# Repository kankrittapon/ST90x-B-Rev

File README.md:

# ST909B-4G V1.0 — โน้ตถอดรหัสบอร์ด 4G GPS Tracker (v3)

บอร์ดจริง: **ST909B-4G-V1.0** (silkscreen, วันที่ผลิต 20230816) — แทร็กเกอร์ 4G/GPS ใช้แบตเตอรี่ Li-ion 1 ก้อน
ชิปหลัก: A7670SA (4G LTE Cat-1, SIMCom) + Quectel L76KB-A58 (GNSS) + TP4056 (ชาร์จ) + MCU ตระกูล LQFP-48 (ด้านหลัง, **ถูกถอดออกไปแล้ว**)

เอกสารละเอียดแยกฝั่ง:
- [Front_PCB.md](Front_PCB.md) — ฝั่งหน้า (โมดูล RF, SIM, วงจรชาร์จ, จุดทดสอบ/บริการ)
- [Back_PCB.md](Back_PCB.md) — ฝั่งหลัง (MCU, เสาอากาศ GPS แบบแผ่น, จุดบัดกรีสายเข้าเคส)

เอกสารงาน PCB (ใน `ST909B-4G\`):
- [docs/P3-ROUTING.md](ST909B-4G/docs/P3-ROUTING.md) — เส้นทาง P3 ที่ล็อกแล้ว: ตาราง segment รายชิ้น + กติกา clearance + ข้อพิสูจน์
- [docs/GND-ISLANDS.md](ST909B-4G/docs/GND-ISLANDS.md) — เกาะ GND 4 ชิ้น: โครงสร้าง fill, สาเหตุ, การเย็บ stitching via, วิธี probe
- [docs/P4-SILKSCREEN.md](ST909B-4G/docs/P4-SILKSCREEN.md) — ล้าง silkscreen 42 → 0: กติกากันชน + ตารางย้าย ref/rect ทั้งหมด + sync lib
- [docs/DRC-LOG.md](ST909B-4G/docs/DRC-LOG.md) — วิวัฒนาการ DRC ทุกรอบ + warning ที่ยอมรับ (ตอนนี้เหลือ 2) พร้อมเหตุผล
- `export\` — CSV สถานะล่าสุด (components / nets_pads / routes / drc_violations) + PDF schematic/layers/BOM
- `archive\` — dump ดิบ `.out.txt` (55 ไฟล์) ทุกรอบแก้ + `pads_dump.txt` — ใช้อ้างอิงย้อนหลังเท่านั้น
- `scripts\` — สคริปต์แก้บอร์ด/ตรวจทั้งหมด (หัวไฟล์มีโน้ตการออกแบบ) • รายงาน DRC ปัจจุบันอยู่ที่ `ST909B-4G_drc_violations.json` (รากโปรเจกต์ — อย่าย้าย)

---

## ภาพอ้างอิง (8 ไฟล์)

| ไฟล์ | คำอธิบาย |
|---|---|
| `ภาพทำเองด้านหน้า.jpg` | ภาพวาดฝั่งหน้า + ป้ายกำกับ (แก้ตามรูปจริงแล้ว = v2) |
| `ภาพทำเองด้านหลัง.jpg` | ภาพวาดฝั่งหลัง + ป้ายกำกับ (แก้ตามรูปจริงแล้ว = v2) |
| `ด้านหน้า(บน).jpg` | รูปถ่ายจริงฝั่งหน้าส่วนบน (โมดูล A7670SA, 220µF, +SPK, BOOT) |
| `ด้านหน้า(กลาง).jpg` | รูปถ่ายจริงฝั่งหน้าส่วนกลาง (GPS L76KB, G3V3, SIM slot, LRX/LTX) |
| `ด้านหน้า(ล่าง).jpg` | รูปถ่ายจริงฝั่งหน้าส่วนล่าง (TP4056, M3V3, ขาบริการขอบล่าง) |
| `ด้านหลัง(บน).jpg` | รูปถ่ายจริงฝั่งหลังส่วนบน (ANT-4G, SOS, LED GPS/CHR/4G) |
| `ด้านหลัง(กลาง).jpg` | รูปถ่ายจริงฝั่งหลังส่วนกลาง (แผ่นเสาอากาศ GPS, 0Ω ×2) |
| `ด้านหลัง(ล่าง).jpg` | รูปถ่ายจริงฝั่งหลังส่วนล่าง (MCU footprint, shield fence, MIC) |

---

## สรุปสถานะ (ตรวจครบทุกภาพแล้ว)

### ✅ ยืนยันแล้วจากรูปจริง
- โมดูล **A7670SA** พร้อมข้อมูลฉลากครบ (ดู [Front_PCB.md](Front_PCB.md))
- โมดูล **Quectel L76KB-A58** (ฉลากมาร์ค `L76KB-A58 / 01-C1003`)
- ตัวเก็บประจุ tantalum **220µF / 6.3V** (มาร์ค "220 6.3V") บริเวณ VBAT
- **Nano SIM slot** แบบกด (แบรนด์ MUP, ป้าย LOCKED/OPEN)
- **TP4056** บริเวณล่างขวา + ตัวต้านทานมาร์ค `R200` ข้างตัว (PROG)
- **ANT-4G 2 ขา (RF + GND)** — หน้าซ้ายบน / หลังขวาบน เป็นคู่เดียวกันผ่านทะลุบอร์ด
- **ปุ่ม SOS** ฝั่งหลัง + ชุดวงจร LED ติดป้าย `GPS / CHR / 4G`
- **แผ่นเสาอากาศ GPS เซรามิก** มาร์ค `204003` มี pad feed ตรงกลาง
- **0Ω Jumpers ×2** (มาร์ค "0 0") ข้างไอคอนเสาอากาศฝั่งหลัง — *ไม่ใช่* Battery Voltage Divider
- **Shield-can fence**: แถบ pad รูปตัว L รอบบริเวณ MCU ฝั่งหลัง
- **ลำดับ pad ขอบล่างฝั่งหน้า** *(ยืนยันใหม่ใน v3)*: ซ้าย→ขวา = `GND / URX / UTX / +5V` แล้ว `PKEY` เป็นปุ่ม 2 pads แยกขวาสุด
- **M3V3 pad**: pad ซ้ายสุดในแถว 3 จุด ตรงป้าย M3V3
- **G3V3**: ป้าย + pad ทดสอบ ของเส้น 3.3V ฝั่ง GPS (มี LDO ตัวเล็ก SOT-23 ใกล้เคียง)
- Silkscreen `ST909B-4G-V1.0` / `20230816` ฝั่งหลัง

### ⚠️ สันนิษฐาน (ตำแหน่งถูก แต่ยืนยันตัวตน/ค่าไม่ได้)
- **Level Shifter (1.8V–3.3V)**: v3 อัปเดต — เห็นชิปดำตัวเล็กบริเวณขวาของโมดูลตรง callout แล้ว (แก้จาก v2 ที่สรุปว่าไม่เห็น) แต่ marking ยังอ่านไม่ได้
- **22R ×4** (มาร์ค "220" สี่ตัวในแถวเดียว) — น่าจะเป็นตัวต้านทานอนุกรมสาย UART/USB ที่วิ่งลง MCU ด้านหลัง
- **TP4056 ตัวจริง**: มาร์คบน IC อ่านไม่ชัด สรุปชื่อจากตำแหน่ง + Rprog เท่านั้น
- **R200**: ถ้าค่าจริงเป็น 2.0k (ตามภาพวาด) → กระแสชาร์จ TP4056 ≈ 600 mA; ต้องวัดด้วยมัลติมิเตอร์เพื่อปิดจบ
- **ขนาดแผ่นเสาอากาศ GPS ~25×25 mm** — ตามภาพวาด ยังไม่ได้วัดจริง
- **จุดป้าย `GND / BAT / PKEY` ขอบล่างฝั่งหลัง** — อ้างจากภาพวาด (ในรูปจริงเห็นชัดแค่ `MIC`)
- **ตำแหน่ง Buck/LDO footprint ว่าง** (ฝั่งหลัง ขวาของ MCU) — เห็น footprint ว่างตรงบริเวณตามภาพวาด แต่รูปแบบ pad ยังจับคู่กับชนิด IC ไม่ได้

### ❓ ยังแก้ไม่ได้
- รุ่น/ตัวตน **MCU** (LQFP-48 ถูกถอดแล้ว ไม่มีหลักฐานรุ่น)
- ฟังก์ชัน **SOT-23 IC** ใกล้ ANT-4G ฝั่งหลัง (v1 เคยเดาว่า "Power Switch IC" — ไม่มีหลักฐาน)
- ฟังก์ชัน **0Ω ×2** (จัมเปอร์อะไร / อยู่บนเส้นสัญญาณใด)
- ฟังก์ชัน pad **GTX** และ **Quectel test pad** (น่าจะเป็นจุดทดสอบ UART ของ GPS)
- ชิ้นส่วนที่ **ถูกถอด/ขูดออก**: MCU, ชุด Buck/LDO, และบริเวณเหนือ `+SPK` (ผิว mask ฉีกขาว 2 แถบ — พบใหม่ใน v3)

---

## สถานะการสร้างใน KiCAD (12 พ.ย. 2026)

โปรเจกต์: `ST909B-4G\ST909B-4G.kicad_pro` — สร้าง/แก้ผ่าน KiCAD MCP (SWIG backend, เซฟลงดิสก์ทุกขั้น)

- **Board outline**: สี่เหลี่ยม **35 × 74 mm** ⚠️ ประมาณจากเคส 78×39 มม. หักกำแพง ~2 มม./ข้าง — รอวัดจริง
- **ชิ้นส่วนที่วางแล้ว 34 รายการ** (ตำแหน่งทั้งหมด ⚠️ ชั่วคราว ตามสัดส่วนรูปถ่าย):
  - หน้า (F.Cu): `U1` A7670SA block 24×24 • `C1` tantalum 220µF block 7.3×4.3 • `U2` L76KB block 10.1×9.7 • `J1` SIM slot block 12.4×11.6 • `U3` TP4056 SOP-8 block • `ANT1` 2 pads (RF+GND) • `J2` 4 pads GND/URX/UTX/+5V • `SW1` PKEY 2 pads • `J6` +SPK 2 pads • `J7` BOOT 3 pads • `J3` VBUS/DP/DM 3 pads • `J4` M3V3 3 pads • `J5` BAT pad 4×3 • `TP1` LRX • `TP2` LTX • `TP3` GTX • `TP4` Quectel TP • `RN1` 22R×4 (footprint จริง 4x0603) • `U5` Level Shifter (SOT-23-6 จริง) • `U6` GPS LDO (SOT-23 จริง) • `R3` R200 (0603 จริง)
  - หลัง (B.Cu): `U4` **LQFP-48 7×7 footprint มาตรฐานจริง** (ตัวแทน MCU ที่ถูกถอด) • `AE2` GPS patch block 18×18 ⚠️ (ภาพวาดบอก 25×25 แต่การสเกล 2 ทางชี้ ~18×18) • `R1`+`R2` 0603 ค่า 0 (จัมเปอร์ ×2) • `SW2` SOS (2 pads + body) • `LED1`–`LED3` 0603 จริง (GPS/CHR/4G) • `U7` SOT-23 ขับ LED (fn?) • `TP5`–`TP8` ขอบล่าง MIC/GND/BAT/PKEY
- **คลัง footprint โปรเจกต์**: `lib\ST909B.pretty` (footprint ทำเอง 15 ตัว: block modules, pad groups, test pads) — ลงทะเบียนใน `fp-lib-table` ทั้งโปรเจกต์และ global
- ชิ้นที่ใช้ footprint มาตรฐาน: LQFP-48 (`Package_QFP`), R_0603 ×3 (`Resistor_SMD`), R_Array_Convex_4x0603 (`Resistor_SMD`), SOT-23 / SOT-23-6 ×2 (`Package_TO_SOT_SMD`), LED_0603 ×3 (`LED_SMD`)
- ยังไม่ได้วาง: shield-can fence รอบ MCU (แถบ pad รูป L — ทำพร้อม phase routing), GPS antenna via (เป็น via เดี่ยว ไม่ใช่ component), footprint Buck/LDO ที่ถูกถอด (ยังจับคู่ชนิด IC ไม่ได้)
- หมายเหตุเทคนิค: `place_component` ของ MCP เคย resolve คลังโปรเจกต์ไม่ได้ (LibraryManager อ่านตารางคลังครั้งเดียวตอนถูกสร้าง) — แก้ด้วยการ trigger สร้าง manager ใหม่ จากนั้นใช้งานได้ปกติทั้งคลังโปรเจกต์และคลังมาตรฐาน

## Netlist reconstruction (12 พ.ย. 2026)

- **Schematic จำลอง**: `ST909B-4G.kicad_sch` — 34 components ตรงกับบอร์ดทุกตัว (จับคู่ด้วย ref) • ต่อ net ด้วย label บน pin ตรงจุด (115 labels, ไม่ใช้ wire — local label ชื่อเดียวกันใน sheet เดียว = net เดียวกันตามกติกา KiCad)
- **คลัง symbol**: `lib\ST909B.kicad_sym` (13 symbol ทำเอง, ลงทะเบียน project scope): `U1_A7670SA` (17 pins), `U2_L76KB`, `U3_TP4056`, `U4_MCU_LQFP48` (17 pins กลุ่มหน้าที่), `U5_LEVELSHIFT`, `U6_LDO_SOT23`, `U7_LEDDRV`, `RN1_ARRAY4`, `J1_SIM6` (C1/C2/C3/C5/C6/C7), `J2_SERVICE4`, `J6_SPK2`, `ANT1_ANT4G`, `PADS_ROW3` • ส่วน R/C/LED/SW/TestPoint ใช้ symbol มาตรฐาน (`Device`, `LED`, `Switch`, `Connector`)
- **Pinout ทั้งหมดเป็นการสันนิษฐาน** ⚠️ ตามการวิเคราะห์เส้นทางบนบอร์ดใน `Front_PCB.md`/`Back_PCB.md` — รอ datasheet A7670SA/L76KB เพื่อยืนยัน
- **PWR_FLAG ×6** (`#FLG1`–`#FLG6`): ปักไว้ที่ +5V / GND / VBAT / VDD_EXT / SIM_VDD / USB_VBUS เพื่อไม่ให้ ERC ติด power-pin error กับ net ที่ถูกขับจาก IC ภายใน block
- **สถานะ net (ตรวจแล้ว 2 ฝั่ง)**: บอร์ด 37 nets / 73 pads ตรงแผน 100% • schematic netlist (kicad-cli) 54 nets — ทุก net ที่มี pad บนบอร์ดตรง PLAN ทุก pin, ส่วนเพิ่มคือ pin ของ block component (U1/U2/U3/C1/J1) ที่ไม่มี pad จริงตามดีไซน์ — ดูแผนฉบับเต็มใน `scripts\assign_nets_v1.py` (PLAN)
- **ERC (kicad-cli)**: **0 errors** • 65 warnings ที่ตั้งใจยอมรับ: 40 `endpoint_off_grid` (pin symbol ทำเองไม่ตรง grid), 15 `lib_symbol_mismatch` (cache ใน .sch ต่างจาก lib เชิงคอสเมติก), 10 `isolated_pin_label` (net ขาเดียวที่ตั้งใจ: TEMP, MIC_N, SIM_VPP, R1_A/B, R2_A/B, QUECTEL_TP, MCU_UTX/URX4G)
- **DRC baseline** (ยังไม่เดิน track): 85 รายการ — 36 `unconnected_items` (รอ routing), 20 `silk_overlap` + 23 `silk_over_copper` (block footprint ชั่วคราว), 5 `courtyards_overlap` + 1 `clearance` (R1↔R2 ชิด 0.05 มม., TP4/TP5/TP7/U4 ชนขอบเพื่อนบ้าน) ⚠️ ตำแหน่งชั่วคราว จะเก็บตอน routing/วัดจริง
- ⚠️ **บั๊ก MCP ที่พบและวิธีข้าม**:
  - `sync_schematic_to_board` map net ผิด (GND/VBAT หาย, pad ได้ net เพี้ยน) → กำหนด net ตรงด้วย pcbnew script แทน
  - `batch_add_and_connect` **วาง symbol ทุกตัวที่ (0,0)** + label ใช้พิกัด local ของ symbol → ทุก component ทับกัน, label ซ้อนกัน, net หลอมรวมเป็นก้อนเดียว → แก้ด้วย `fix_sch_layout.py` (ย้าย instance + สร้าง label ใหม่ตรง pin endpoint, สูตร `sheet = (X+libx, Y−liby)`)
- **สคริปต์ใน `scripts\`**:
  - `assign_nets_v1.py` — แผน net→pads ฉบับเต็ม (authoritative) + สั่งกำหนดจริง (71/71 pad)
  - `assign_nets_fix1.py` — แก้ 2 pad ที่ SetNet ไม่ติดรอบแรก (`R3/2→/GND`, `U4/9→/LED_EN`)
  - `fix_sch_layout.py` — ซ่อมเลย์เอาต์ schematic (ย้าย 40 instances, label 115 จุด, no-connect 9 จุด) + backup `.sch.bak-pre-layout`
  - `fix_pin_types.py` — แก้ pin type ผิด (TX→output, A1/A2→bidirectional, GND/VBUS/SIM_VDD→passive) ใน .sch + .sym
  - `net_check.py` — export/parse netlist ด้วย kicad-cli แล้วเทียบกับ PLAN
  - `erc_summary.py`, `erc.json`, `drc_report.json`, `ST909B-4G_drc_violations.json` — ผลตรวจ
- วิธีตรวจ net ที่เชื่อถือได้: pcbnew script หรือ kicad-cli (`D:\KiCad\10.0\bin\python.exe` / `kicad-cli.exe`) — เครื่องมือ `get_net_pads` ของ MCP คืน 0 เสมอ (ชื่อ net บนดิสก์มี prefix `/` เช่น `/GPS_TX`)

## Routing (13 พ.ย. 2026) — v4b เสร็จ: **DRC 0 errors**

- **สถิติบอร์ด**: 99 tracks (F 47 / B 52) + 24 vias + GND copper zones 2 ชั้น (F.Cu + B.Cu เติม fill ครบ) • มิติเส้น: สัญญาณ 0.25 มม., VBAT 0.3 มม., via Ø0.6 / drill 0.3, ช่องไฟร์ขั้นต่ำ 0.2 มม. (ตรง 0.2 พอดีผ่าน DRC — พิสูจน์แล้วหลายจุด)
- **โครง routing หลัก**: MCU ฝั่งหลัง (B.Cu) ต่อตรงแถว pad ขวาของ U4; สาย USB ต่าง ๆ เดินกำแพง F.Cu ลง via ข้ามชั้น; 4G_TXD/4G_RXD เป็น trunk บน F.Cu ขอบขวา; LED_GPS วนลัดกำแพงเสาอากาศฝั่งหลัง; GND ประสานด้วย via (16.5,58.5) เย็บเกาะใต้ U4 เข้ากับโซน F และ (29.5,45.0) ต่อโซนหลัก F↔B *(อัปเดต: ปัจจุบัน via (16.5,58.5) ถูกใช้เป็นเส้น /M3V3 — สถานะและเหตุผลดู [docs/DRC-LOG.md](ST909B-4G/docs/DRC-LOG.md))*
- **Keepout เสาอากาศ GPS (AE2)**: B.Cu ห้าม track/via/pad ใน x 2.5..20.5, y 35..53 — เส้น GPS_RX ฝั่ง B เลาะขอบตะวันตกที่ x=2.25 (กฎ MCP: สนามผ้าเส้นเดียวชนขอบ = ผ่าน ตัดเข้าไปเท่านั้นที่ผิด)
- **การเดินทางของ DRC ต่อ error**: v2 = 45 (triage ครบ) → v3 = 15 (6 crossing + 4 short ใหม่จาก jog ผิดฝั่ง) → v4 = 4 → **v4b = 0** • เหลือ warning ที่ตั้งใจยอมรับ: silk 42 (block footprint ชั่วคราว) + via_dangling 1 (GPS_RF @ 11.5,44.0 — โครงสร้างเดิมของบอร์ดจริงใน keepout เสาอากาศ เติมไม่ได้ตั้งแต่ต้น)
- **บทเรียน geometry ที่ค้นพบจาก DRC** (สำคัญกับการวัดจริง):
  - pad แถวขวา/บน/ล่างของ U4 กว้าง **1.475 มม. ตามแกน x** (x-span 20.43..21.90) — ไม่ใช่ 0.3; มาจาก orientation pad ใน footprint LQFP-48 ที่แก้โดยให้ DRC ตัดสิน
  - U6/1–2 ก็ยาวตามแกน x (3.325..4.800) → เส้น x=3.4 ลัดวงจร, x=2.95 ผ่าน • ช่อง TP4 (ขอบขวา 2.80) ↔ U6/1 กว้าง 0.525 < 0.65 ที่ track 0.25 ต้องการ → แก้ด้วย local jog ไป x=3.2 เฉพาะช่วง y 50.5..60 (จบใน pad TP3 เน็ตเดียวกัน)
  - starved_thermal U4/2: pad GND แถวขวาถูกเพื่อนบ้านปิดจนมีสไป้ก์เดียว → ขยับเส้น GPS_TX จาก x=22.25 → x=22.9 เปิด fill ช่องตะวันออกกว้าง 0.4745 ได้ 2 สไป้ก์
- **ขั้นตอนบังคับของ workflow**: refill zone ต้องแยก process (script แก้เส้น: UnFill + save → process ใหม่: `ZONE_FILLER.Fill` + save) — Fill ใน process เดียวกับการ `b.Delete` จะ segfault; DRC สั่งผ่าน MCP (`run_drc`) อ่านผลจาก JSON
- **สคริปต์ routing** (ลำดับใช้จริง): `route_tracks_v1.py` → `route_fix_v2.py` (เดินครบ 85+21) → `route_fix_v3.py` (patch 20+6 → 35+7) → `route_fix_v4.py` (patch 28+5 → 25+5) → `route_fix_v4b.py` (แก้ 4 error สุดท้าย: 5+2 → 7+3) • เครื่องมือตรวจ: `dump_all_pads.py`, `diag_v4.py` (โครงสร้าง pad/via รายจุด)
- ⚠️ **เน็ต single-pad ที่ยังลอย (รอตัดสิน route-or-leave)**: `R1_A/B`, `R2_A/B`, `ANT_4G_RF`, `B_VBUS`, `MIC_P`, `K_P/K_N`, `VDD_EXT`, `G_TXD_1V8`, `G_RXD_1V8`, `MCU_UTX4G/URX4G`, `QUECTEL_TP`, `R3/1` — DRC ไม่ฟ้อง unconnected (เน็ตลอยเดี่ยว) แต่ในบอร์ดจริงเส้นพวกนี้มีปลายทางต่อ ต้องรอ pinout จริงเมื่อวัดบอร์ด/datasheet
- ⚠️ **ยังไม่ทำ**: GND stitching grid เสริม (~5 มม. — ตอนนี้ GND ต่อครบแล้ว เป็น optional), shield-can fence รอบ MCU

## P2.5 — Gate ตัวโมดูล U1/U2 (13 พ.ย. 2026) — **0 errors, gate ปิดแล้ว**

กติกาใหม่ (มติโครงการ): **F.Cu ห้ามมี track/via ใต้ตัวโมดูล** U1 (center ±12 มม.) และ U2 (±4.85×5.05) — B.Cu ใต้โมดูลยอมให้ • เกณฑ์ผ่าน = DRC 0 error (clearance/keepout/shorting/mask/hole/edge/crossing/courtyard) — warning ยกไป P4

- **เดินทาง error: 12 → 6 → 0** (สามรอบแก้: `p25b_fix` → `p25c_fix` → `p25d_clean`) ตรวจด้วย `kicad-cli pcb drc --severity-all` เท่านั้น (checker เขียนเองพิสูจน์แล้วว่ามี 2 บั๊ก)
- **ข้อค้นพบสำคัญ**:
  - **Board edge clearance = 0.5000 มม.** (จาก board setup) → ทองแดงต้องห่างขอบบอร์ด ≥0.5 — เส้น x=34.60 เดิมล้ำ (จริง 0.275) → แก้เป็น x=34.30 (ขอบเส้น 34.425 เว้น 0.575)
  - CrtYd จริงของ U6 (ดัมพ์ polygon): bbox (3.08..6.92, 43.20..46.59 ตอน center 44.90) — ค่าเดิมที่เดาจาก `GetBoundingBox` ผิดทั้งชุด ต้องวัดจาก polygon เสมอ
  - p25b ลบได้ 33/34 เพราะ DEL list ใส่ layer `B` แต่เส้นจริงเป็น `F` → เส้นผี /LED_GPS F.Cu (23.60,58.00)→(23.60,30.10) ตกค้าง (dangling สองข้าง) ลบท้ายรอบด้วย `p25d_clean`
- **การแก้รอบสุดท้าย**:
  - `/LED_4G` เส้นใหม่: B.Cu v x=34.30 (68.10→6.90) → via (33.90,6.90) → F.Cu hop h y=6.90 ลัดเหนือ SOS h_top → F.Cu v x=25.40 (6.90→14.80) → via (25.40,14.80) → B.Cu h y=14.80 → v x=17.71 ลง LED3.2 — ทุกช่องเว้น ≥0.225 (U1 pads 0.475, LED_EN x=26.05 0.40, J7.1 0.575, LED_CHR 0.40)
  - `U6` ย้าย (5.00,44.90)→(5.00,44.15): CrtYd 42.45..45.84 เว้น U2 CrtYd (ล่าง 46.10) = 0.26 และ J3 CrtYd (บน 41.99) = 0.46 + ปรับมุม /VBAT เป็น (1.00,44.15) — pad1/2 ของ U6 เว้น 0.50
  - `U1 pad39` starved_thermal (spoke 1/2 — ล้อมด้วย pad ไร้เน็ตช่อง 0.40 กลืนด้วย clearance 0.2×2, ฝั่ง E โดน LED_CHR/LED_EN ปิด) → ตั้ง **zone connection = FULL** (แผ่นเชื่อมตรง — มาตรฐาน GND ของ RF module)
- **สถานะปัจจุบัน**: 95 tracks + 21 vias • DRC **0 error** / 44 warning ยอมรับ (silk 42 + via_dangling 2 — ไป P4) • **unconnected 15** = punch list ของ P3
- ⚠️ **ห้ามเซฟทับไฟล์บอร์ดจาก KiCad GUI ที่เปิดค้างอยู่** (จะกลับสถานะ zone fill / track)

**P3 punch list (15 unconnected)**: G3V3 (U6.2↔U2.8) • VBAT (trk↔U1.55/56/57) • GPS_TX (U2.3↔trk 7.00,37.00) • USB_VBUS (J3.1↔U1.24) • PKEY (trk 17.75,71.50↔U1.1) • GPS_RX (web B.Cu↔TP2.1 และ↔U2.2) • ANT_4G_RF (ANT1.1↔U1.60) • VDD_EXT (U1.15↔U5.1) • 4G_TXD_1V8 (U1.9↔U5.2) • 4G_RXD_1V8 (U1.10↔U5.3) • USB_DP_M (trk↔U1.27) • USB_DM_M (trk↔U1.28)

---

## P3 — เดินเส้น criticals ที่เหลือ + ซ่อมเกาะ GND (14 พ.ย. 2026) — **0 errors, unconnected 0**

เดินเส้นเพิ่ม 6 เน็ต (batch 1–2 ทำก่อนหน้า, batch 3–4 รอบนี้) ตรวจเชิงตัวเลขครบด้วย `scripts/p3_verify.py` (44 candidates / 0 violation) ก่อนลงบอร์ดทุกครั้ง

- **batch 3 (`scripts/p3_batch3.py`)** — ⑦ PKEY + ⑪ VDD_EXT + ⑫ 4G_TXD_1V8 + ⑬ 4G_RXD_1V8 (21 tracks + 8 vias):
  - **PKEY**: via-in-pad U1.1 (1.70,9.50) → F lane ตะวันตก **x=0.60 w0.20** (ขอบทองแดง 0.50 = edge clearance พอดี) ลงถึง y 29.35 → via (1.65,29.35) → B ลงช่องแคบ x=1.625 (เว้น 0.20 พอดีทั้งซ้าย–ขวา: via VBAT (1.00,44.15) กับ via GPS_RX) → ขึ้น y=60.10 → x=10.15 → ลง y=66.30 → x=4.00 → y=70.40 → เข้า via เกาะ (17.75,70.40)
  - **VDD_EXT**: via-in-pad U1.15 (1.70,23.50) → B v x=1.70 → h y=25.00 → v x=27.70 → via-in-pad U5.1 (27.70,32.05)
  - **TXD**: via-in-pad U1.9 → B h y=17.50 → v x=2.80 → h y=22.00 → v x=29.35 → via (29.35,33.00) → F stub เข้า U5.2
  - **RXD**: via-in-pad U1.10 → B h y=18.50 → v x=2.35 → h y=24.30 → v x=28.50 → via-in-pad U5.3 (28.50,33.95)
- **batch 4 (`scripts/p3_batch4.py`)** — ⑭⑮ USB_DP_M/DM_M (11 tracks + 3 vias): ออกจากแถวใต้ U1 (14.00/15.00,28.90) → B แยกเลน DP (x=25.00) / DM (x=24.10) ลงเกาะ USB ฝั่งใต้ (DP เข้าเลน B เดิม y=57.75, DM via (24.30,57.00) → F → via เกาะ (19.90,58.00))
- **batch 5 (`scripts/p3_batch5_fix.py`) — ซ่อม 2 เกาะ zone-fill ที่ DRC รายงาน unconnected 2 คู่**:
  - รากเหตุ (จาก dump vertex ของ fill outline): **เกาะ B** = แถบล่าง/เส้นด้ายตะวันตก ถูกกรงด้วยเส้น PKEY B ใหม่ (x=1.625 ปิดช่อง fill x 1.35..2.03, ต่อด้วยกำแพง VBAT/M3V3 เดิม) — pad เดียวในเกาะคือ TP6.1 (B) • **เกาะ F** = บล็อก NE (x 25.73..34.5 × y 7.2..31.7) + แถบตะวันออก (x 34.03..34.5 × y 32..73.4) ถูกปิดด้วย anti ของ LED_4G/LED_CHR/LED_EN F ที่แตะกันพอดีที่ x=25.725 — pad เดียวคือ J7.3 (F-SMD)
  - แก้ด้วย **GND stitching via 2 ตัว** (ยืนยัน fill ด้วย `scripts/p3_probe.py` ก่อน): **(2.50,71.20)** = F main + B เกาะ และ **(30.00,15.00)** = F เกาะ + B main → ครบ 4 fill เชื่อมกันผ่าน via /GND เดิม (29.50,45.00) → **unconnected 2 → 0** (รายละเอียดใน [docs/GND-ISLANDS.md](docs/GND-ISLANDS.md))
- **starved_thermal U1.2** (error ตัวเดียวที่เหลือ): lane PKEY F ต้องผ่าน corridor ตะวันตกกว้าง 0.70 (x 0.50..1.20) จึงปิด spoke ตะวันตกของ pad2 เสมอ (ตะวันตกของเลนไม่มี fill: ขอบ zone 0.50 กับ anti เลน 0.30..0.90; N/S ถูก anti pad ข้างเคียงปิดตายโครงสร้าง — เหมือน pad39 ที่แก้ใน P2.5) → ตั้ง **U1.2 zone connection = FULL** (`scripts/p3_pad2_solid.py`) → error หาย
- **สถานะปัจจุบัน**: **153 tracks + 42 vias** • DRC **0 error / 45 warning** (silk 42 + via_dangling 3: M3V3 (16.50,58.50), PKEY via-in-pad (1.70,9.50) [F-only โดยเจตนา — ทุกทางเส้น B ถูกกำแพง via-in-pad ปิดหมด], GPS_RF (11.50,44.00)) • **unconnected 0** • ⚠️ ยังห้ามเซฟทับจาก GUI ค้าง

**รอ**: การวัดสัดส่วนจากผู้ใช้ (P1) + ตาราง net ลอย (J1 SIM pads, AE2 pads, pinout V1.03) ก่อนปลดล็อก P5 (Gerber)

## P4 — ล้าง silkscreen 42 ข้อ + เก็บกวาด via (17 พ.ย. 2026) — **2 warnings, 0 errors**

แก้ silk ทั้ง 42 ข้อให้หมด (กลยุทธ์ออกแบบบนค่าจริงของบอร์ด: edge clearance 0.5 / mask opening = ขนาด pad / min silk text height 0.8) — สรุปเต็มใน [docs/P4-SILKSCREEN.md](docs/P4-SILKSCREEN.md)

- **ย้าย Reference 21 จุด** — J2–J7, SW1, SW2, ANT1, C1, TP1–8, U4, R1, R2 (พ้น silk rect/pad mask ของตัวเอง); U4 ขยับไปขวาบน (21.60,52.65) หนี rect ใหญ่ AE2
- **ขยาย silk rect 14 อัน** — TP1–8 (pad+0.5), ANT1, J3, J4, J7, SW2 ให้ล้อม pad โดย stroke ห่าง mask opening 0.15–0.20 (J2/SW1/J5/J6/C1 ไม่แตะ — rect เดิมผ่านอยู่แล้ว)
- **U1 pin-1 poly** ย้ายเข้าหน้าต่างขอบตะวันตก [0.5..1.2] เป็นสามเหลี่ยม (0.60,9.20)-(0.60,9.80)-(1.10,9.50) — รูปเดิมยื่นเลยขอบ (x −0.10) และย่อไม่ได้เพราะ edge clearance 0.5
- **ฟอนต์ LED1–3** 1.0 → 0.8 (ผ่านเกณฑ์ min 0.8 พอดี) + LED2 แยกแถวขึ้น (15.50,10.50) — ที่ 0.8 กว้าง 3.22 > pitch 3.0 จึงซ้อนแถวกันไม่ได้
- **ลบ via /M3V3 (16.50,58.50)** — via_dangling 3 → 2; track F y=58.50 ยังต่อเนื่อง (via 42 → 41)
- **sync lib 6 footprint** (TP_PAD_1.2/1.5, PADS_ROW_3, ANT_4G_PADS, SW_SOS, A7670SA_LGA88) — จัดการ lib_footprint_mismatch 14 ข้อที่เกิดหลังแก้บอร์ด; J7 rect ปรับ y ±0.80 ให้ใช้ lib PADS_ROW_3 ตัวเดียวกับ J3/J4 ได้
- ตรวจซ้ำหลังจบ: DRC **2 violations (via_dangling PKEY by design + GPS_RF รอ P1) / 0 error / 0 unconnected / parity 0** • `p3_verify.py` 44 candidates / 0 • refill zone แล้ว (2 fill) • export CSV ใหม่ (153 tracks / 41 vias / 35 footprints)

**รอ** (ไม่เปลี่ยน): P1 การวัดจริง + ตาราง net ลอย → ปลดล็อก GPS_RF เดินเส้น + P5 Gerber

---

## ประวัติการแก้

### v8 (รอบนี้ — P4 ปิด: silk 0 / warning เหลือ 2)
- ✅ **P4 ปิด**: silkscreen 42 → **0** (ย้าย ref 21 จุด • ขยาย rect 14 อัน • ย้าน U1 pin-1 poly • ฟอนต์ LED 0.8) — DRC **2 violations / 0 error / 0 unconnected / parity 0** (via_dangling 2 ที่ยอมรับ)
- 🔧 ลบ via /M3V3 (16.50,58.50) (3→2) • sync lib 6 footprint จัดการ lib_footprint_mismatch 14 ข้อ • refill zone + export CSV ใหม่ (41 vias)
- 📚 เอกสารเพิ่ม [docs/P4-SILKSCREEN.md](ST909B-4G/docs/P4-SILKSCREEN.md) + DRC-LOG/README อัปเดตสถานะ • dump `p4_*.out.txt` → `archive\` • สคริปต์ใหม่ `p4_*.py` 7 ตัว
- ⏳ เหลือ P5 Gerber — บล็อกด้วย P1 (การวัดขอบบอร์ด/pad AE2) จากผู้ใช้

### v7 (P3 ปิด: 0 error / 0 unconnected)
- ✅ **P3 ปิด**: เดินครบ 6 criticals (PKEY / VDD_EXT / 4G_TXD_1V8 / 4G_RXD_1V8 / USB_DP_M / USB_DM_M) — unconnected 15 → **0**
- 🔧 ซ่อม 2 เกาะ GND ด้วย stitching via (2.50,71.20) + (30.00,15.00) — ตรวจ fill ด้วย point-in-poly ก่อนทุกจุด • lane PKEY F ขยับ x=0.80→0.60 w0.20 (ขอบ 0.50 พอดี) • U1.2 zone connection = FULL แก้ starved_thermal ตามแนว pad39
- 📤 สถานะ: **153 tracks + 42 vias**, DRC 45 warning ยอมรับ (silk 42 + via_dangling 3) — เหลือ P4 silkscreen → P5 Gerber (รอการวัด P1 จากผู้ใช้)
- 🧹 เคลียร์ไฟล์: dump ดิบ 55 ไฟล์ + pads_dump → `archive\` • เอกสารสะอาด 3 ไฟล์ใน `docs\` (P3-ROUTING / GND-ISLANDS / DRC-LOG) • สคริปต์ตรวจเพิ่ม `p3_gnd_graph.py` (parse บอร์ดตรง: เน็ต via ทั้งหมด + ยืนยันไม่มี TH pad)

### v6 (P2.5 gate โมดูล ปิดแล้ว)
- ✅ **P2.5 gate ปิด: DRC 0 error** (12→6→0) — F.Cu ว่างใต้ U1/U2 ครบ, ทองแดงห่างขอบบอร์ด ≥0.5 มม. ทุกเส้น
- 🔧 แก้หลัก: /LED_4G เส้นใหม่ (v x=34.30 + F.Cu hop หน้า SOS + ลง v x=25.40), U6 →(5.00,44.15) ตาม CrtYd จริง, U1 pad39 zone connection = FULL, ลบเส้นผี /LED_GPS (บั๊กใส่ layer ผิดใน DEL list ของ p25b)
- 📤 export CSV ใหม่ (tracks 95 / vias 21 / footprints 35) • punch list P3 = 15 unconnected

### v5 (routing v4b)
- ✅ **Routing ครบทุกเน็ต multi-pad**: 99 tracks + 24 vias + GND zone 2 ชั้น — **DRC 0 errors / 43 warnings ที่ยอมรับ** (เดินทางต่อ error: 45 → 15 → 4 → 0)
- 🔧 จุดแก้สำคัญรอบสุดท้าย (v4b): local jog GPS_RX หนีช่อง TP4↔U6/1 (x=3.2), stub B ของ via (7.0,34.5), ขยับ GPS_TX x=22.25→22.9 แก้ starved_thermal U4/2, ลบ via (22.0,45.0) เน็ตเพี้ยน + เติม via GND ประสาน 2 จุด ((16.5,58.5), (29.5,45.0))
- ⚠️ ค้างรอ: เน็ต single-pad ลอย 13 กลุ่ม (route-or-leave — รอ pinout จริง), GND stitching grid, shield-can fence รอบ MCU

### v4 (netlist + ERC/DRC)
- ✅ **Net บนบอร์ดครบสมบูรณ์**: 37 nets / 73 pads ตรง PLAN 100% (แก้ 2 pad ค้าง: R3/2→GND, U4/9→LED_EN)
- 🛠 **ซ่อม schematic ที่พังจากบั๊ก MCP**: symbol ทุกตัวถูกวางซ้อนที่ (0,0) + label หลุดพิกัด → net หลอมเป็นก้อนเดียว (79 pins ใน +5V) — ย้าย instance 40 ตัว + label 115 จุดตรง pin (A4 portrait) แล้ว netlist จาก kicad-cli ตรง PLAN ทุก pin
- ✅ **ERC 0 errors** (เดิม 7 errors จาก pin type ผิด — แก้ TX/A1/A2/GND/VBUS/SIM_VDD)
- 📊 **DRC baseline**: 85 รายการ (unconnected 36 รอ routing, silk 43, courtyard/clearance 6 จากตำแหน่งชั่วคราว)
- 🚫 ปัก no-connect 9 ขา: RN1 5–8, U4 16–17, U3 STDBY/CHRG/CE (สันนิษฐานไม่ใช้ ⚠️)

### v3 (ตรวจครบทั้ง 8 ภาพ)
- ✅ **ลำดับ pad ขอบล่าง**: ก่อนหน้านี้รอรูปจริงส่วนล่าง — ตอนนี้มี `ด้านหน้า(ล่าง).jpg` แล้ว ยืนยันว่าภาพวาดตรง (`GND/URX/UTX/+5V` + PKEY ปุ่ม 2 pads)
- ⚠️→ **Level Shifter**: จาก v2 ที่ว่า "ไม่เห็นชิป QFN" → ใน `ด้านหน้า(บน).jpg` เห็นชิปดำตัวเล็กตรงตำแหน่งแล้ว (แต่ยังอ่าน marking ไม่ได้ จึงไม่ปิดสถานะ)
- ➕ เพิ่มข้อสังเกต: บริเวณเหนือ `+SPK` ฝั่งหน้ามีร่องขูด/ชิ้นส่วนถูกถอด (สัมพันธ์กับ "คราบตะกั่ว" ที่ v2 พบ)
- 📄 แยกเอกสารรายฝั่ง: `Front_PCB.md`, `Back_PCB.md`

### v2 (ก่อนหน้า — แก้ภาพวาดตามรูปถ่ายจริง)
- `"Battery Voltage Divider" → "0Ω Jumpers ×2"`: รูปจริงพิมพ์ว่า "0" ทั้งสองตัว จึงเป็นจัมเปอร์ ไม่ใช่วงจรแบ่งแรงดัน
- `"Power Switch IC" → "SOT-23 IC (function?)"`: จากรูปไม่มีหลักฐานว่าเป็น power switch จึงไม่ระบุหน้าที่
- ➕ `"Shield-can fence"`: แถบ pad รูปตัว L รอบบริเวณ MCU คือฐานฝาครอบกันสัญญาณรุ่นที่ไม่ได้ใส่ฝา
- `"LDO 3.3V" → "GPS LDO (G3V3)"`: ให้ตรงกับ silkscreen จริงที่เขียนว่า G3V3
- ➕ `"M3V3 pad"`: pad ซ้ายสุดในแถว 3 จุด ตรงตำแหน่งตัวอักษร M3V3 บนบอร์ดจริง

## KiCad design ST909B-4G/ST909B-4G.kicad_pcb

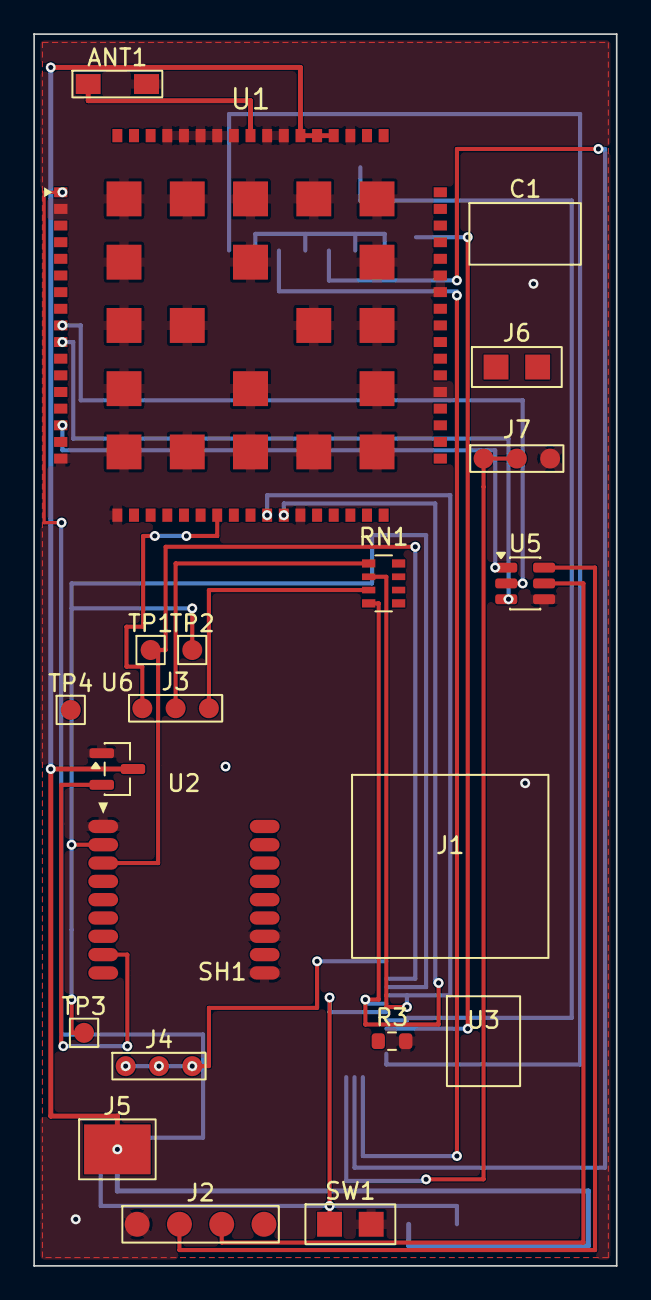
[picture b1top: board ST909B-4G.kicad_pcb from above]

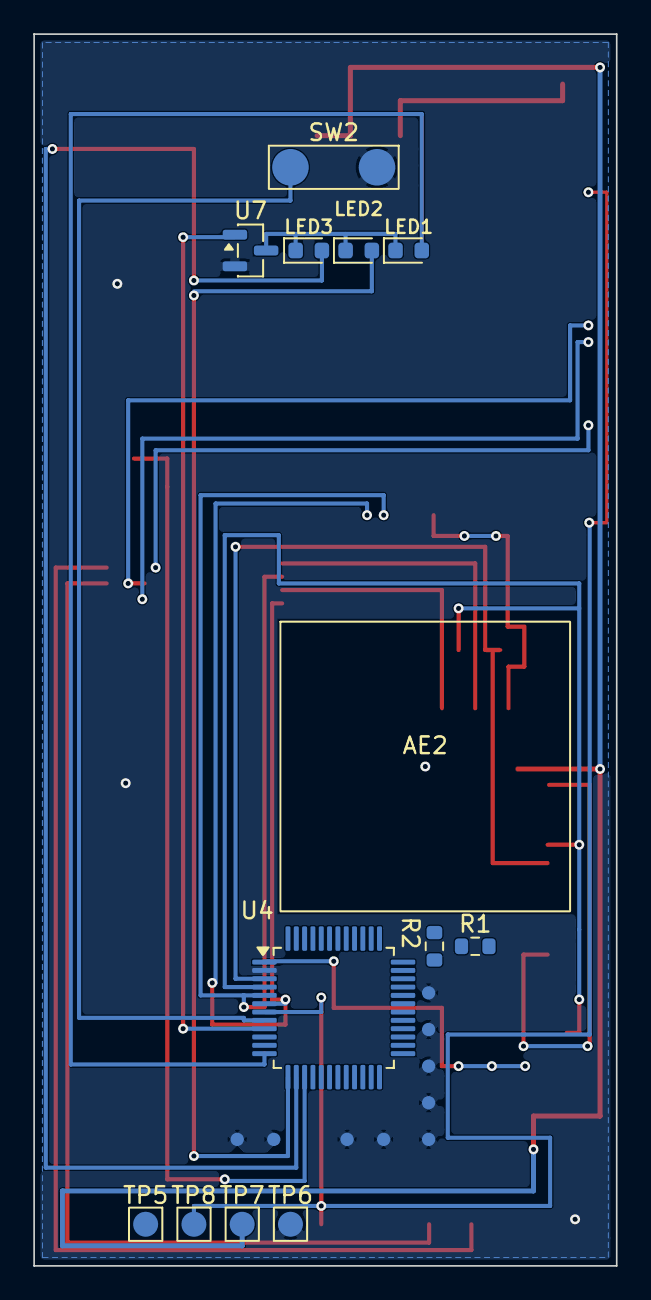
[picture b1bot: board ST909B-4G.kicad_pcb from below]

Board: 2 copper layers, 35.0 x 74.0 mm, 35 parts (13 on the bottom side), 25 nets.

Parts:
AE2: GPS patch; GPS_PATCH_BLOCK
ANT1: ANT-4G; ANT_4G_PADS
C1: 220uF/6.3V; CAP_TANT_220U_BLOCK
J1: SIM nano; SIM_NANO_PUSH
J2: GND/URX/UTX/+5V; PADS_SERVICE_4
J3: VBUS/DP/DM; PADS_ROW_3
J4: M3V3 x3; PADS_ROW_3
J5: BAT; BAT_PAD
J6: +SPK; SPK_2PAD
J7: BOOT; PADS_ROW_3
LED1: GPS; LED_0603_1608Metric
LED2: CHR; LED_0603_1608Metric
LED3: 4G; LED_0603_1608Metric
R1, R2: 0?; R_0603_1608Metric
R3: 2.0k?; R_0603_1608Metric
RN1: 22R x4?; R_Array_Convex_4x0603
SH1: SHIELD_FENCE
SW1: PKEY; SW_PKEY_2PAD
SW2: SOS; SW_SOS
TP1: LRX; TP_PAD_1.2
TP2: LTX; TP_PAD_1.2
TP3: GTX; TP_PAD_1.2
TP4: Quectel TP; TP_PAD_1.2
TP5: MIC; TP_PAD_1.5
TP6: GND; TP_PAD_1.5
TP7: BAT; TP_PAD_1.5
TP8: PKEY; TP_PAD_1.5
U1: A7670SA; A7670SA_LGA88
U2: L76KB-A58; L76KB_LGA18
U3: TP4056?; IC_SO8_BLOCK
U4: MCU? (LQFP-48); LQFP-48_7x7mm_P0.5mm
U5: LevelShift?; SOT-23-6
U6: GPS LDO 3.3V; SOT-23
U7: LED drv?; SOT-23

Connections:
/4G_RXD_1V8: U1.10, U5.3
/4G_RXD_3V3: J2.3, U5.5
/4G_TXD_1V8: U1.9, U5.2
/4G_TXD_3V3: J2.2, U5.6
/ANT_4G_RF: ANT1.1, U1.60
/BOOT: J7.1, J7.2, U4.15
/G3V3: U2.8, U6.2
/GND: ANT1.2, J2.1, J7.3, R3.2, SH1.1, SH1.2, SH1.3, SH1.4, SH1.5, SH1.6, SH1.7, SH1.9, SH1.10, SW1.2, SW2.2, TP6.1, U1.2, U1.17, U1.18, U1.29, U1.39, U1.45, U1.46, U1.54, U1.58, U1.59, U1.61, U1.62, U1.63, U1.64, U1.65, U1.69, U1.70, U1.71, U1.72, U1.73, U1.74, U1.75, U1.76, U1.77, U1.78, U1.79, U1.80, U1.81, U1.82, U1.83, U1.84, U1.85, U1.86, U1.87, U1.88, U2.1, U2.10, U2.12, U4.2, U5.4, U6.1, U7.2
/GPS_RX: TP2.1, TP3.1, U2.2, U4.4
/GPS_TX: TP1.1, U2.3, U4.3
/LED_4G: LED3.2, U4.14
/LED_CHR: LED2.2, U4.13
/LED_EN: U4.9, U7.1
/LED_GPS: LED1.2, U4.12
/LED_K: LED1.1, LED2.1, LED3.1, U7.3
/M3V3: J4.1, J4.2, J4.3, U4.1
/PKEY: SW1.1, TP8.1, U1.1, U4.7
/SOS: SW2.1, U4.8
/USB_DM_F: J3.3, RN1.3
/USB_DM_M: RN1.4, U1.28, U4.6
/USB_DP_F: J3.2, RN1.1
/USB_DP_M: RN1.2, U1.27, U4.5
/USB_VBUS: J3.1, U1.24
/VBAT: J5.1, TP7.1, U1.55, U1.56, U1.57, U6.3
/VDD_EXT: U1.15, U5.1

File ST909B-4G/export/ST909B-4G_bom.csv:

"Reference","Value","Footprint","QUANTITY"
"AE2","GPS patch","ST909B:GPS_PATCH_BLOCK","1"
"ANT1","ANT-4G","ST909B:ANT_4G_PADS","1"
"C1","220uF/6.3V","ST909B:CAP_TANT_220U_BLOCK","1"
"J1","SIM nano","ST909B:SIM_NANO_PUSH","1"
"J2","GND/URX/UTX/+5V","ST909B:PADS_SERVICE_4","1"
"J3","VBUS/DP/DM","ST909B:PADS_ROW_3","1"
"J4","M3V3 x3","ST909B:PADS_ROW_3","1"
"J5","BAT","ST909B:BAT_PAD","1"
"J6","+SPK","ST909B:SPK_2PAD","1"
"J7","BOOT","ST909B:PADS_ROW_3","1"
"LED1","GPS","LED_SMD:LED_0603_1608Metric","1"
"LED2","CHR","LED_SMD:LED_0603_1608Metric","1"
"LED3","4G","LED_SMD:LED_0603_1608Metric","1"
"R1","0?","Resistor_SMD:R_0603_1608Metric","1"
"R2","0?","Resistor_SMD:R_0603_1608Metric","1"
"R3","2.0k?","Resistor_SMD:R_0603_1608Metric","1"
"RN1","22R x4?","Resistor_SMD:R_Array_Convex_4x0603","1"
"SW1","PKEY","ST909B:SW_PKEY_2PAD","1"
"SW2","SOS","ST909B:SW_SOS","1"
"TP1","LRX","ST909B:TP_PAD_1.2","1"
"TP2","LTX","ST909B:TP_PAD_1.2","1"
"TP3","GTX","ST909B:TP_PAD_1.2","1"
"TP4","Quectel TP","ST909B:TP_PAD_1.2","1"
"TP5","MIC","ST909B:TP_PAD_1.5","1"
"TP6","GND","ST909B:TP_PAD_1.5","1"
"TP7","BAT","ST909B:TP_PAD_1.5","1"
"TP8","PKEY","ST909B:TP_PAD_1.5","1"
"U1","A7670SA","ST909B:A7670SA_MODULE","1"
"U2","L76KB-A58","ST909B:L76KB_MODULE","1"
"U3","TP4056?","ST909B:IC_SO8_BLOCK","1"
"U4","MCU? (LQFP-48)","Package_QFP:LQFP-48_7x7mm_P0.5mm","1"
"U5","LevelShift?","Package_TO_SOT_SMD:SOT-23-6","1"
"U6","GPS LDO 3.3V","Package_TO_SOT_SMD:SOT-23","1"
"U7","LED drv?","Package_TO_SOT_SMD:SOT-23","1"
